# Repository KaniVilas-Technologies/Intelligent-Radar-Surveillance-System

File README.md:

# Intelligent-Radar-Surveillance-System
A smart embedded surveillance platform designed for real-time environmental scanning, object detection, and intelligent monitoring using ultrasonic sensing technology.

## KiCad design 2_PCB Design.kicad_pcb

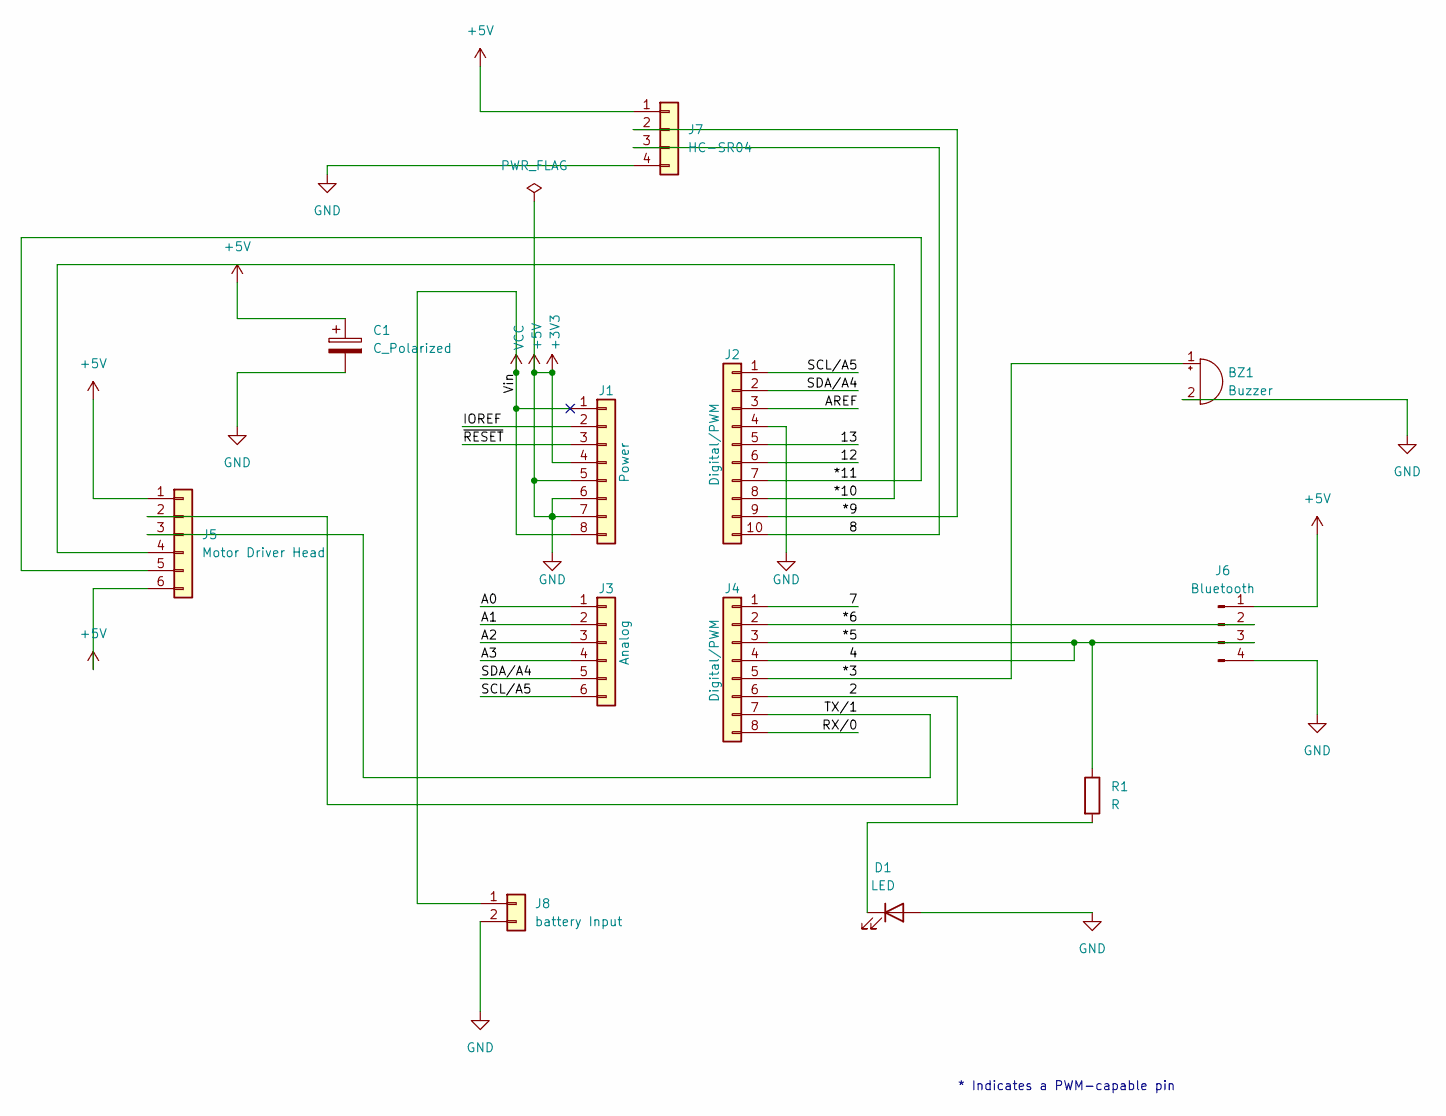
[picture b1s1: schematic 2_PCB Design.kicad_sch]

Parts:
BZ1: Buzzer; Buzzer_12x9.5RM7.6
C1: C_Polarized; CP_Radial_D5.0mm_P2.00mm
D1: LED; LED_D5.0mm
J1: Power; PinSocket_1x08_P2.54mm_Vertical
J2: Digital/PWM; PinSocket_1x10_P2.54mm_Vertical
J3: Analog; PinSocket_1x06_P2.54mm_Vertical
J4: Digital/PWM; PinSocket_1x08_P2.54mm_Vertical
J5: Motor Driver Head; PinHeader_1x06_P2.54mm_Vertical
J6: Bluetooth; PinHeader_1x04_P2.54mm_Vertical
J7: HC-SR04; PinHeader_1x04_P2.54mm_Vertical
J8: battery Input; PinHeader_1x02_P2.54mm_Vertical
R1: R; R_Axial_DIN0207_L6.3mm_D2.5mm_P7.62mm_Horizontal

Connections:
+3V3: BZ1.2 (-), C1.1, C1.2, D1.2 (A), J1.4, J1.5, J1.6, J1.7, J2.4, J5.1, J5.6, J6.1, J6.4, J7.1, J7.4, J8.2
/2: J4.6, J5.2
/7: J4.1
/8: J2.10, J7.3
/12: J2.6
/13: J2.5
/*3: BZ1.1 (+), J4.5
/*5: J4.3, J4.4, J6.3, R1.1
/*6: J4.2, J6.2
/*9: J2.9, J7.2
/*10: J2.8, J5.4
/*11: J2.7, J5.5
/A0: J3.1
/A1: J3.2
/A2: J3.3
/A3: J3.4
/AREF: J2.3
/IOREF: J1.2
/RX/0: J4.8
/SCL/A5: J2.1, J3.6
/SDA/A4: J2.2, J3.5
/TX/1: J4.7, J5.3
/~RESET: J1.3
unnamed: D1.1 (K), R1.2
VCC: J1.1, J1.8, J8.1

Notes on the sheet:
* Indicates a PWM-capable pin

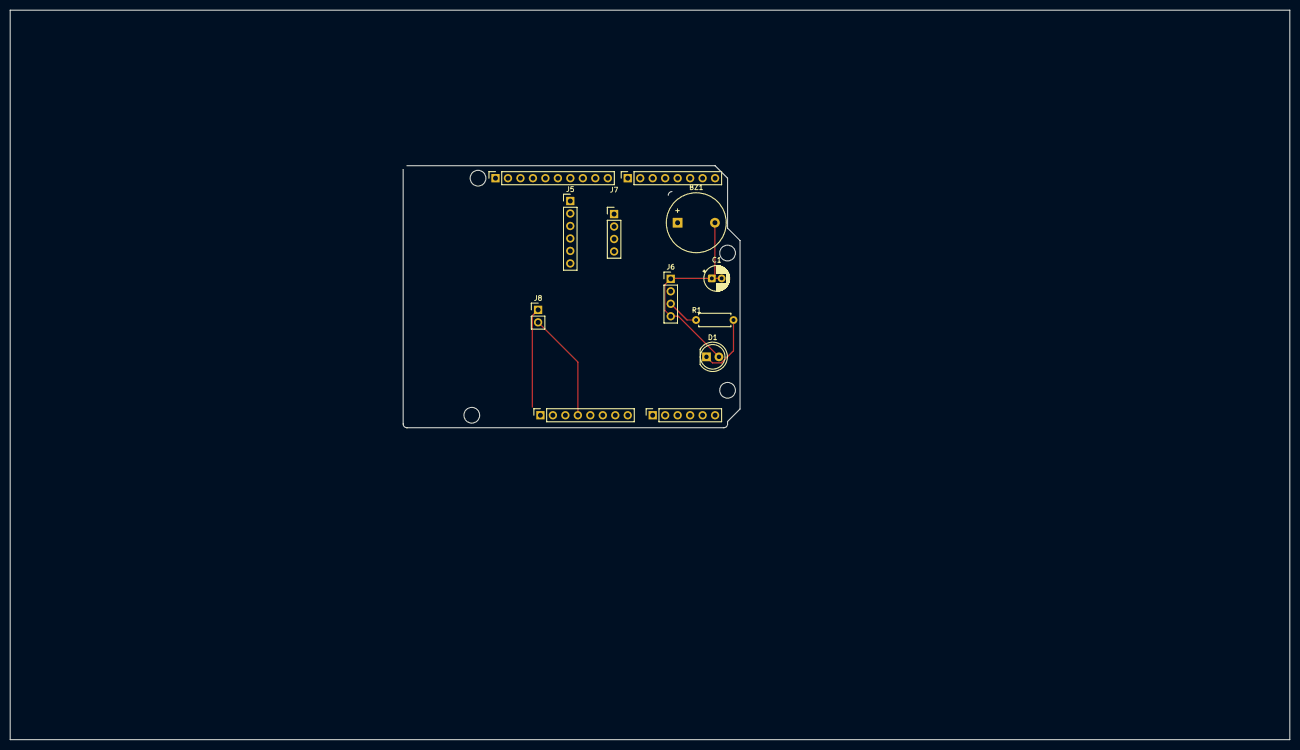
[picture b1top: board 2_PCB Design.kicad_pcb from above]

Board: 2 copper layers, 260.5 x 148.5 mm, 16 parts (0 on the bottom side), 14 nets.

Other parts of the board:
MH1, MH2, MH3, MH4: MountingHole_3.2mm
